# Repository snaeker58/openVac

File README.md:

# OpenVac - a custom motherboard

The goal of this project is to develop a fully functional motherboard to create an open-source autonomous vacuum robot.

 While the current goal is to get a functioning board for the Eufy RoboVac 11, the final goal should be something that can be used/adapted to work in all robot vacuums.

## Roadmap
*Nobody: This probably should go in a seperate file.*
### v0: Concept Phase
- **Goals**:
  - Define project objectives.
  - Determine core functionalities.
- **Basic Structure**:
  - Establish an initial project framework.
- **Key Components**:
  - **Motor Drive Circuit**: Design a DIY motor driver/H-bridge.
  - **Brush Control**: Develop circuits for controlling all cleaning brushes.
  - **Vacuum**: Identify and understand the pinout.
  - **Basic Sensing**: 
    - Understand various sensors.
    - Reverse-engineer the main sensor array.
    - Prototype edge sensors to achieve functionality.
- **Status**: **Finished**

### v0.1: Basic Movement
- **Movement Capabilities**:
  - Implement steering and acceleration.
- **PCB Development**:
  - **DIY Motor Drive Circuit**
  - **Side Brush Control Circuit**
  - **Main Brush Control Circuit**
  - **PWM Vacuum Control**
- **Status**: **Finished**

### v0.2: Minimum Viable Product (MVP)
- **Power & Batteries**:
  - Implement a Battery Management System (BMS).

  - Integrate lithium-ion batteries.

- **Control**:
  - Enable USB serial control for motors, brushes, and vacuum.
- **Miniaturization**:
  - Utilize off-the-shelf components for motor drive, BMS, and more.
- **Status**: **In progress (order placed)**

### v0.3: Basic Sensing
- **Sensor Development**:
  - Finalize cliff sensors (completed in v0).
  - Collect raw data from the main sensor array.
  - Implement a working bumper bar.
- **Sensing PCB**:
  - Develop basic signal processing to output usable data.

### Future Phases
- **Microprocessor Selection**:
  - Evaluate GPIO, analog input requirements, and performance needs.
- **Integration**:
  - **Hardware Integration**: Combine support circuits required by the microprocessor.
  - **Final PCB**: Connect all previous systems into a comprehensive PCB design.

### Far Future Goals
- **Navigational Software**: Create software for autonomous cleaning capabilities.
- **User Interface**: Develop an intuitive interface for easier and more precise control.

### Estimated Timeline
**3 years to infinity.**

## Contributing

If you're  mad enough to want to contribute then just tell me when I'm doing something wrong. I'm completely balling everything if you haven't noticed already. But hey I'm having fun.

"Start big or don't start!"

## Acknowledgements

 - I hereby acknowledge ChatGPT for having formatted my text and without me wanting it reworded my contents to sound more corporate.
 - I hereby acknowledge [Readme.so](https://readme.so) to have helped me make my readme look less ugly.

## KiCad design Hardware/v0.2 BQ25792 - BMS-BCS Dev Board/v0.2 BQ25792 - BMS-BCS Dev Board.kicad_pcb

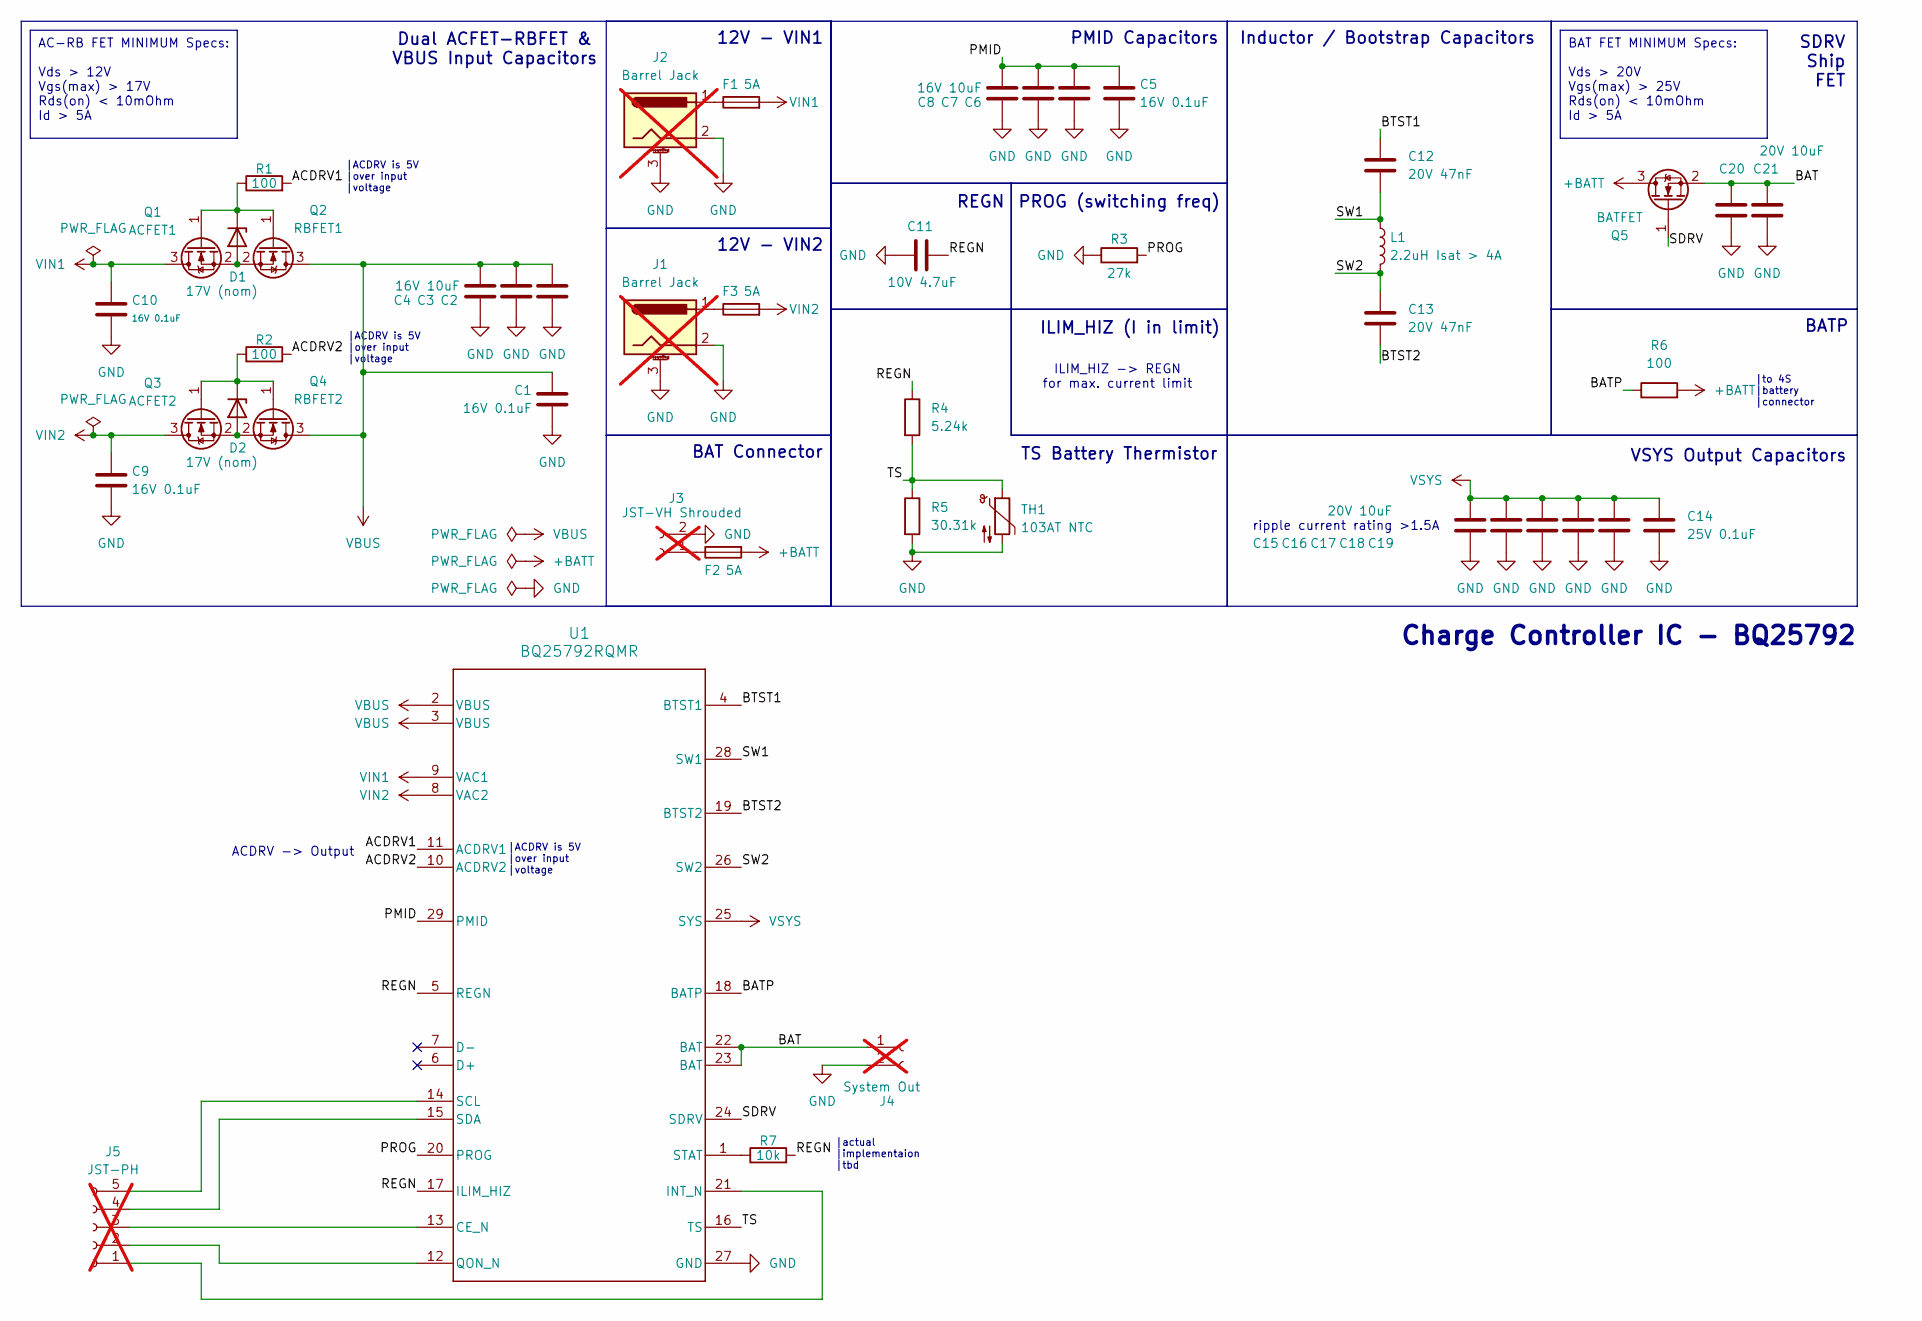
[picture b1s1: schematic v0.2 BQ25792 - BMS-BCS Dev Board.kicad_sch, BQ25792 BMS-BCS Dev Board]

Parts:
C1, C5, C9, C10: 16V 0.1uF; C_0402_1005Metric; LCSC Part Number C22435940
C2, C3, C4, C6, C7, C8: 16V 10uF; C_0603_1608Metric; LCSC Part Number C7472961
C11: 10V 4.7uF; C_0402_1005Metric; LCSC Part Number C466621
C12, C13: 20V 47nF; C_0402_1005Metric; LCSC Part Number C5142571
C14: 25V 0.1uF; C_0402_1005Metric; LCSC Part Number C22435940
C15, C16, C17, C18, C19, C20, C21: 20V 10uF; C_0603_1608Metric; LCSC Part Number C7472961
D1, D2: 17V (nom); D_SOD-123; LCSC Part Number C308704
F1, F2, F3: 5A; Fuse_0603_1608Metric; LCSC Part Number C206961
J1, J2: Barrel Jack; BarrelJack_GCT_DCJ200-10-A_Horizontal; not fitted
J3: JST-VH Shrouded; JST_VH_B2P-VH-FB-B_1x02_P3.96mm_Vertical; not fitted
J4: System Out; JST_VH_B2P-VH-FB-B_1x02_P3.96mm_Vertical; not fitted
J5: JST-PH; JST_PH_B5B-PH-K_1x05_P2.00mm_Vertical; not fitted
L1: 2.2uH Isat > 4A; L_4.5x4.1_H2; LCSC Part Number C22463806
Q1: ACFET1; SOT-23; LCSC Part Number C915719
Q2: RBFET1; SOT-23; LCSC Part Number C915719
Q3: ACFET2; SOT-23; LCSC Part Number C915719
Q4: RBFET2; SOT-23; LCSC Part Number C915719
Q5: BATFET; SOT-23-3L; LCSC Part Number C3033398
R1, R2, R6: 100; R_0402_1005Metric; LCSC Part Number C2906884
R3: 27k; R_0402_1005Metric; LCSC Part Number C2929913
R4: 5.24k; R_0402_1005Metric; LCSC Part Number C11631
R5: 30.31k; R_0402_1005Metric; LCSC Part Number C4156287
R7: 10k; R_0402_1005Metric; LCSC Part Number C2906885
TH1: 103AT NTC; JST_PH_B2B-PH-K_1x02_P2.00mm_Vertical; LCSC Part Number C497233
U1: BQ25792RQMR; RQM0029A-MFG; LCSC Part Number C2862876

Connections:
+BATT: F2.2, Q5.3 (D), R6.2
/ACDRV1: R1.2, U1.11 (ACDRV1)
/ACDRV2: R2.2, U1.10 (ACDRV2)
/BAT: C20.2, C21.2, J4.1, Q5.2 (S), U1.22 (BAT), U1.23 (BAT)
/BATP: R6.1, U1.18 (BATP)
/BTST1: C12.2, U1.4 (BTST1)
/BTST2: C13.1, U1.19 (BTST2)
/PMID: C5.1, C6.2, C7.2, C8.2, U1.29 (PMID)
/PROG: R3.2, U1.20 (PROG)
/REGN: C11.1, R4.1, R7.2, U1.5 (REGN), U1.17 (ILIM_HIZ)
/SDRV: Q5.1 (G), U1.24 (SDRV)
/SW1: C12.1, L1.1, U1.28 (SW1)
/SW2: C13.2, L1.2, U1.26 (SW2)
/TS: R4.2, R5.1, TH1.1, U1.16 (TS)
GND: C1.2, C2.1, C3.1, C4.1, C5.2, C6.1, C7.1, C8.1, C9.2, C10.2, C11.2, C14.2, C15.1, C16.1, C17.1, C18.1, C19.1, C20.1, C21.1, J1.2, J1.3 (MountPin), J2.2, J2.3 (MountPin), J3.2, J4.2, R3.1, R5.2, TH1.2, U1.27 (GND)
unnamed: D1.2 (A), Q1.2 (S), Q2.2 (S)
unnamed: D1.1 (K), Q1.1 (G), Q2.1 (G), R1.1
unnamed: D2.2 (A), Q3.2 (S), Q4.2 (S)
unnamed: D2.1 (K), Q3.1 (G), Q4.1 (G), R2.1
unnamed: F1.1, J2.1
unnamed: F3.1, J1.1
unnamed: F2.1, J3.1
unnamed: J5.1, U1.21 (INT_N)
unnamed: J5.2, U1.12 (QON_N)
unnamed: J5.3, U1.13 (CE_N)
unnamed: J5.4, U1.15 (SDA)
unnamed: J5.5, U1.14 (SCL)
unnamed: R7.1, U1.1 (STAT)
VBUS: C1.1, C2.2, C3.2, C4.2, Q2.3 (D), Q4.3 (D), U1.2 (VBUS), U1.3 (VBUS)
VIN1: C10.1, F1.2, Q1.3 (D), U1.9 (VAC1)
VIN2: C9.1, F3.2, Q3.3 (D), U1.8 (VAC2)
VSYS: C14.1, C15.2, C16.2, C17.2, C18.2, C19.2, U1.25 (SYS)

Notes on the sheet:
BAT FET MINIMUM Specs: Vds > 20V Vgs(max) > 25V Rds(on) < 10mOhm Id > 5A
AC-RB FET MINIMUM Specs: Vds > 12V Vgs(max) > 17V Rds(on) < 10mOhm Id > 5A
TS Battery Thermistor
Inductor / Bootstrap Capacitors
ripple current rating >1.5A
BAT Connector
SDRV Ship FET
|actual |implementaion |tbd
VSYS Output Capacitors
Dual ACFET-RBFET & VBUS Input Capacitors
PROG (switching freq)
|ACDRV is 5V |over input |voltage
ACDRV -> Output
ILIM_HIZ (I in limit)
Charge Controller IC - BQ25792
REGN
12V - VIN1
|to 4S |battery |connector
ILIM_HIZ -> REGN for max. current limit
PMID Capacitors
BATP
12V - VIN2

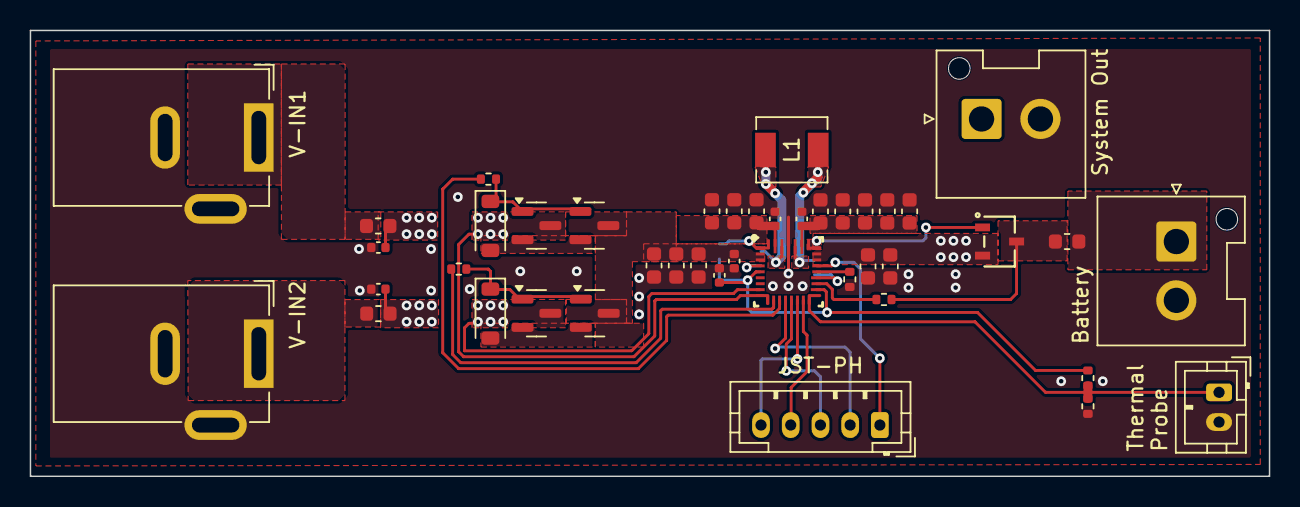
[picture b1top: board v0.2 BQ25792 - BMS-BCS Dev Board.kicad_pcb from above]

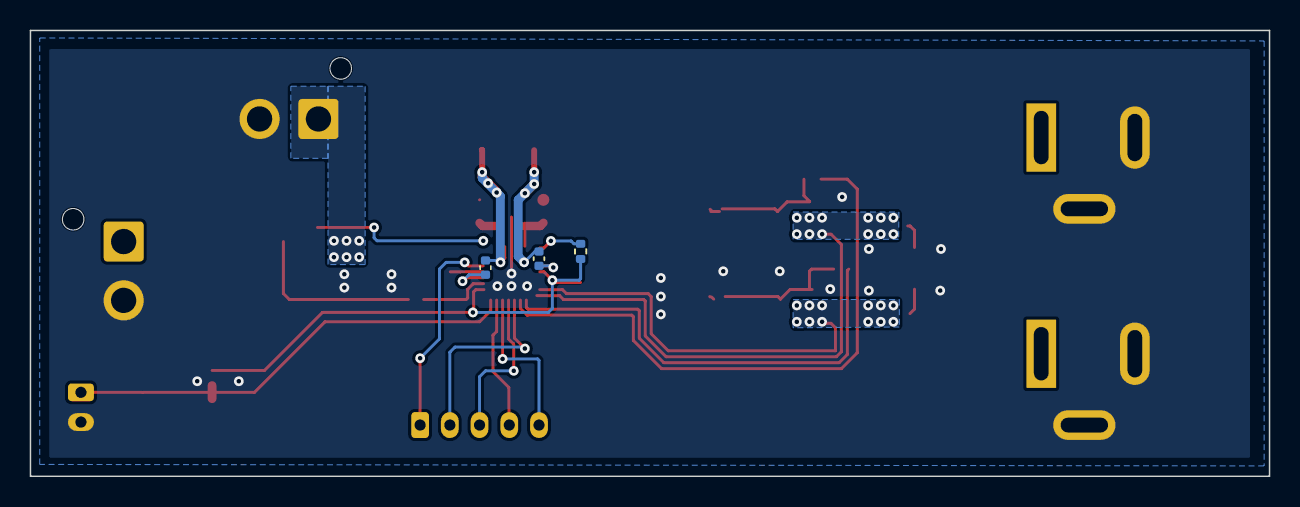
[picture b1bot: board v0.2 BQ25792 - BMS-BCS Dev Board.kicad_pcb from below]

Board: 2 copper layers, 83.4 x 30.0 mm, 46 parts (3 on the bottom side), 32 nets.

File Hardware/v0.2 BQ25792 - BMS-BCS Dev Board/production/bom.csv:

Designator,Footprint,Quantity,Value,LCSC Part #
"C1, C10, C5, C9",0402,4,16V 0.1uF,C22435940
C11,0402,1,10V 4.7uF,C466621
"C12, C13",0402,2,20V 47nF,C5142571
C14,0402,1,25V 0.1uF,C22435940
"C15, C16, C17, C18, C19, C20, C21",0603,7,20V 10uF,C7472961
"C2, C3, C4, C6, C7, C8",0603,6,16V 10uF,C7472961
"D1, D2",D_SOD-123,2,17V (nom),C308704
"F1, F2, F3",0603,3,5A,C206961
L1,L_4.5x4.1_H2,1,2.2uH Isat > 4A,C22463806
Q1,SOT-23,1,ACFET1,C915719
Q2,SOT-23,1,RBFET1,C915719
Q3,SOT-23,1,ACFET2,C915719
Q4,SOT-23,1,RBFET2,C915719
Q5,SOT-23-3L,1,BATFET,C3033398
"R1, R2, R6",0402,3,100,C2906884
R3,0402,1,27k,C2929913
R4,0402,1,5.24k,C11631
R5,0402,1,30.31k,C2998131
R7,0402,1,10k,C2906885
U1,RQM0029A-MFG,1,BQ25792RQMR,C2862876

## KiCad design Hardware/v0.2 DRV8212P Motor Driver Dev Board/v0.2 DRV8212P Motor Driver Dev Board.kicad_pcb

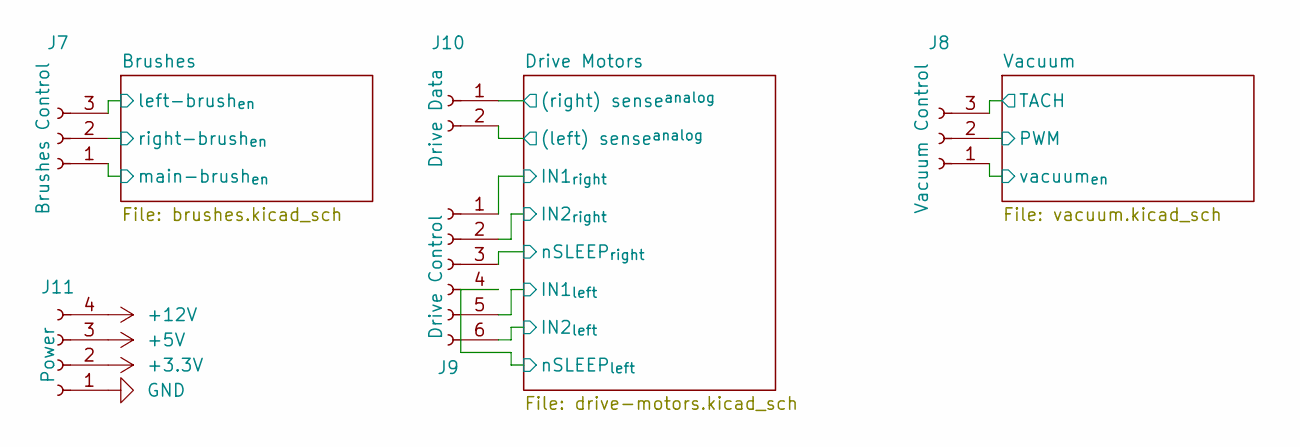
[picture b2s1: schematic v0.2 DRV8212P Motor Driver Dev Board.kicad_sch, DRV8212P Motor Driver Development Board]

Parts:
J7: Brushes Control; JST_PH_B3B-PH-K_1x03_P2.00mm_Vertical
J8: Vacuum Control; JST_PH_B3B-PH-K_1x03_P2.00mm_Vertical
J9: Drive Control; JST_PH_B6B-PH-K_1x06_P2.00mm_Vertical
J10: Drive Data; JST_PH_B2B-PH-K_1x02_P2.00mm_Vertical
J11: Power; JST_PH_B4B-PH-K_1x04_P2.00mm_Vertical

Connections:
+3.3V: J11.2; also elsewhere on the board
+5V: J11.3; also elsewhere on the board
+12V: J11.4; also elsewhere on the board
/Brushes/left-brush_{en}: J7.3; also elsewhere on the board
/Brushes/main-brush_{en}: J7.1; also elsewhere on the board
/Brushes/right-brush_{en}: J7.2; also elsewhere on the board
/Drive Motors/(left) sense^{analog}: J10.2; also elsewhere on the board
/Drive Motors/(right) sense^{analog}: J10.1; also elsewhere on the board
/Drive Motors/IN1_{left}: J9.5; also elsewhere on the board
/Drive Motors/IN1_{right}: J9.1; also elsewhere on the board
/Drive Motors/IN2_{left}: J9.6; also elsewhere on the board
/Drive Motors/IN2_{right}: J9.2; also elsewhere on the board
/Drive Motors/nSLEEP_{left}: J9.4; also elsewhere on the board
/Drive Motors/nSLEEP_{right}: J9.3; also elsewhere on the board
/Vacuum/PWM: J8.2; also elsewhere on the board
/Vacuum/TACH: J8.3; also elsewhere on the board
/Vacuum/vacuum_{en}: J8.1; also elsewhere on the board
GND: J11.1; also elsewhere on the board

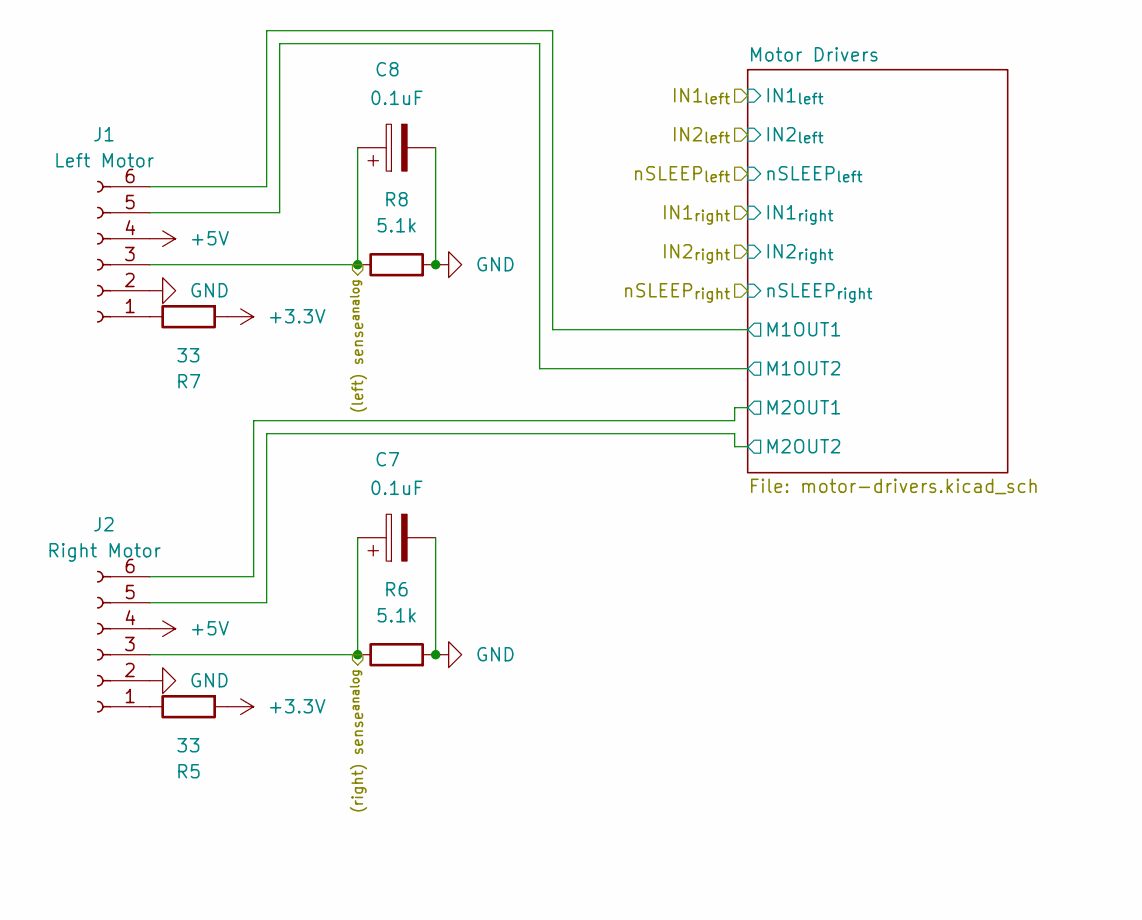
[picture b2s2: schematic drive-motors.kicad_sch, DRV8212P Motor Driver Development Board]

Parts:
C7, C8: 0.1uF; C_0603_1608Metric_Pad1.08x0.95mm_HandSolder
J1: Left Motor; JST_PH_B6B-PH-K_1x06_P2.00mm_Vertical
J2: Right Motor; JST_PH_B6B-PH-K_1x06_P2.00mm_Vertical
R5, R7: 33; R_0603_1608Metric_Pad0.98x0.95mm_HandSolder
R6, R8: 5.1k; R_0603_1608Metric_Pad0.98x0.95mm_HandSolder

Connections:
+3.3V: R5.2, R7.2; also elsewhere on the board
+5V: J1.4, J2.4; also elsewhere on the board
/Drive Motors/(left) sense^{analog}: C8.1, J1.3, R8.1; also elsewhere on the board
/Drive Motors/(right) sense^{analog}: C7.1, J2.3, R6.1; also elsewhere on the board
/Drive Motors/Motor Drivers/M1OUT1: J1.6; also elsewhere on the board
/Drive Motors/Motor Drivers/M1OUT2: J1.5; also elsewhere on the board
/Drive Motors/Motor Drivers/M2OUT1: J2.6; also elsewhere on the board
/Drive Motors/Motor Drivers/M2OUT2: J2.5; also elsewhere on the board
GND: C7.2, C8.2, J1.2, J2.2, R6.2, R8.2; also elsewhere on the board
unnamed: J1.1, R7.1
unnamed: J2.1, R5.1

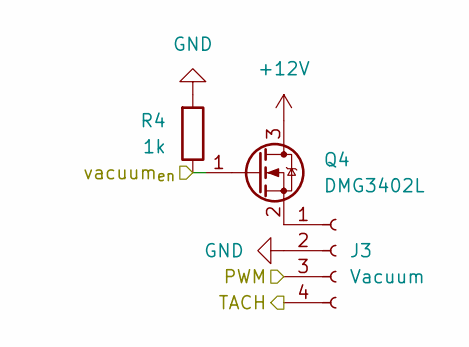
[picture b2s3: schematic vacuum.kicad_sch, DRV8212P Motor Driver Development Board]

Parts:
J3: Vacuum; JST_PH_B4B-PH-K_1x04_P2.00mm_Vertical
Q4: DMG3402L; SOT-23
R4: 1k; R_0603_1608Metric_Pad0.98x0.95mm_HandSolder

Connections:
+12V: Q4.3 (D); also elsewhere on the board
/Vacuum/PWM: J3.3; also elsewhere on the board
/Vacuum/TACH: J3.4; also elsewhere on the board
/Vacuum/vacuum_{en}: Q4.1 (G), R4.1; also elsewhere on the board
GND: J3.2, R4.2; also elsewhere on the board
unnamed: J3.1, Q4.2 (S)

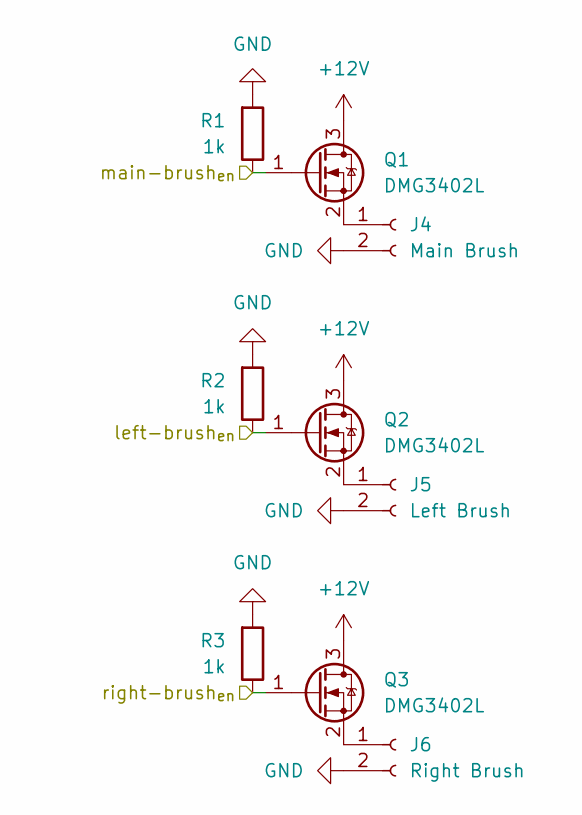
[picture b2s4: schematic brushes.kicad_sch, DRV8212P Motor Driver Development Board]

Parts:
J4: Main Brush; JST_PH_B2B-PH-K_1x02_P2.00mm_Vertical
J5: Left Brush; JST_PH_B2B-PH-K_1x02_P2.00mm_Vertical
J6: Right Brush; JST_PH_B2B-PH-K_1x02_P2.00mm_Vertical
Q1, Q2, Q3: DMG3402L; SOT-23
R1, R2, R3: 1k; R_0603_1608Metric_Pad0.98x0.95mm_HandSolder

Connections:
+12V: Q1.3 (D), Q2.3 (D), Q3.3 (D); also elsewhere on the board
/Brushes/left-brush_{en}: Q2.1 (G), R2.1; also elsewhere on the board
/Brushes/main-brush_{en}: Q1.1 (G), R1.1; also elsewhere on the board
/Brushes/right-brush_{en}: Q3.1 (G), R3.1; also elsewhere on the board
GND: J4.2, J5.2, J6.2, R1.2, R2.2, R3.2; also elsewhere on the board
unnamed: J4.1, Q1.2 (S)
unnamed: J5.1, Q2.2 (S)
unnamed: J6.1, Q3.2 (S)

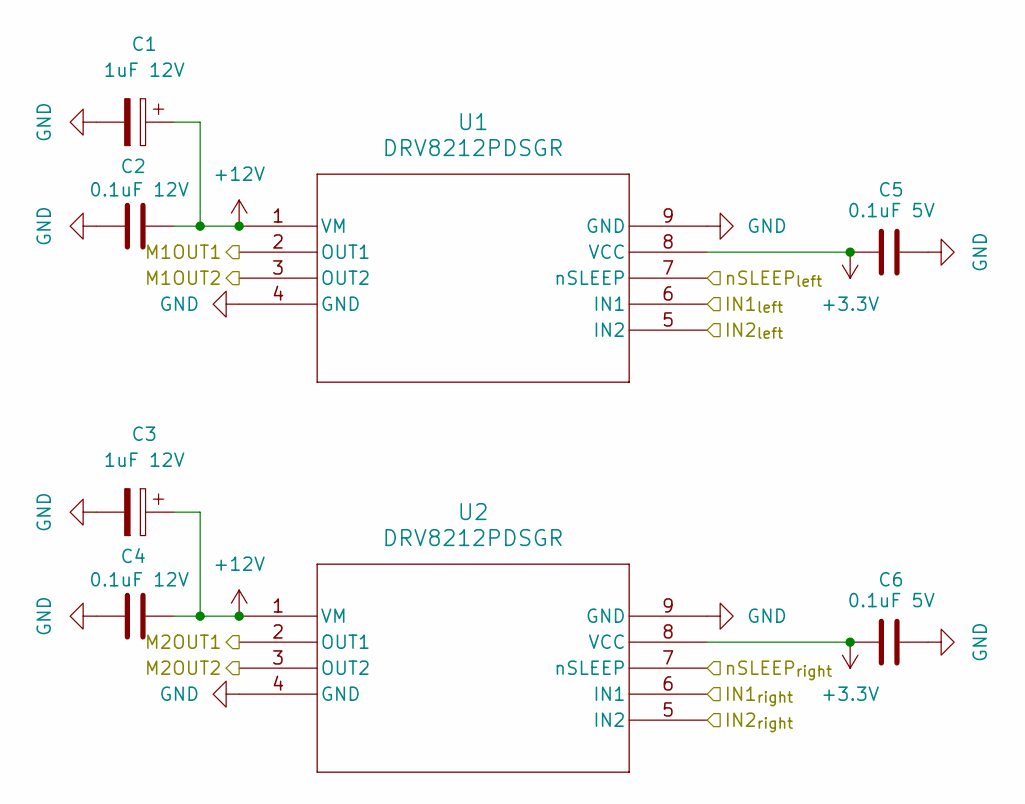
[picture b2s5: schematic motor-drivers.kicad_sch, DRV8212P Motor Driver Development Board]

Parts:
C1, C3: 1uF 12V; C_0603_1608Metric_Pad1.08x0.95mm_HandSolder
C2, C4: 0.1uF 12V; C_0603_1608Metric_Pad1.08x0.95mm_HandSolder
C5, C6: 0.1uF 5V; C_0603_1608Metric_Pad1.08x0.95mm_HandSolder
U1, U2: DRV8212PDSGR; WSON8_DSG_TEX

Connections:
+3.3V: C5.1, C6.1, U1.8 (VCC), U2.8 (VCC); also elsewhere on the board
+12V: C1.1, C2.1, C3.1, C4.1, U1.1 (VM), U2.1 (VM); also elsewhere on the board
/Drive Motors/IN1_{left}: U1.6 (IN1); also elsewhere on the board
/Drive Motors/IN1_{right}: U2.6 (IN1); also elsewhere on the board
/Drive Motors/IN2_{left}: U1.5 (IN2); also elsewhere on the board
/Drive Motors/IN2_{right}: U2.5 (IN2); also elsewhere on the board
/Drive Motors/Motor Drivers/M1OUT1: U1.2 (OUT1); also elsewhere on the board
/Drive Motors/Motor Drivers/M1OUT2: U1.3 (OUT2); also elsewhere on the board
/Drive Motors/Motor Drivers/M2OUT1: U2.2 (OUT1); also elsewhere on the board
/Drive Motors/Motor Drivers/M2OUT2: U2.3 (OUT2); also elsewhere on the board
/Drive Motors/nSLEEP_{left}: U1.7 (nSLEEP); also elsewhere on the board
/Drive Motors/nSLEEP_{right}: U2.7 (nSLEEP); also elsewhere on the board
GND: C1.2, C2.2, C3.2, C4.2, C5.2, C6.2, U1.4 (GND), U1.9 (GND), U2.4 (GND), U2.9 (GND); also elsewhere on the board

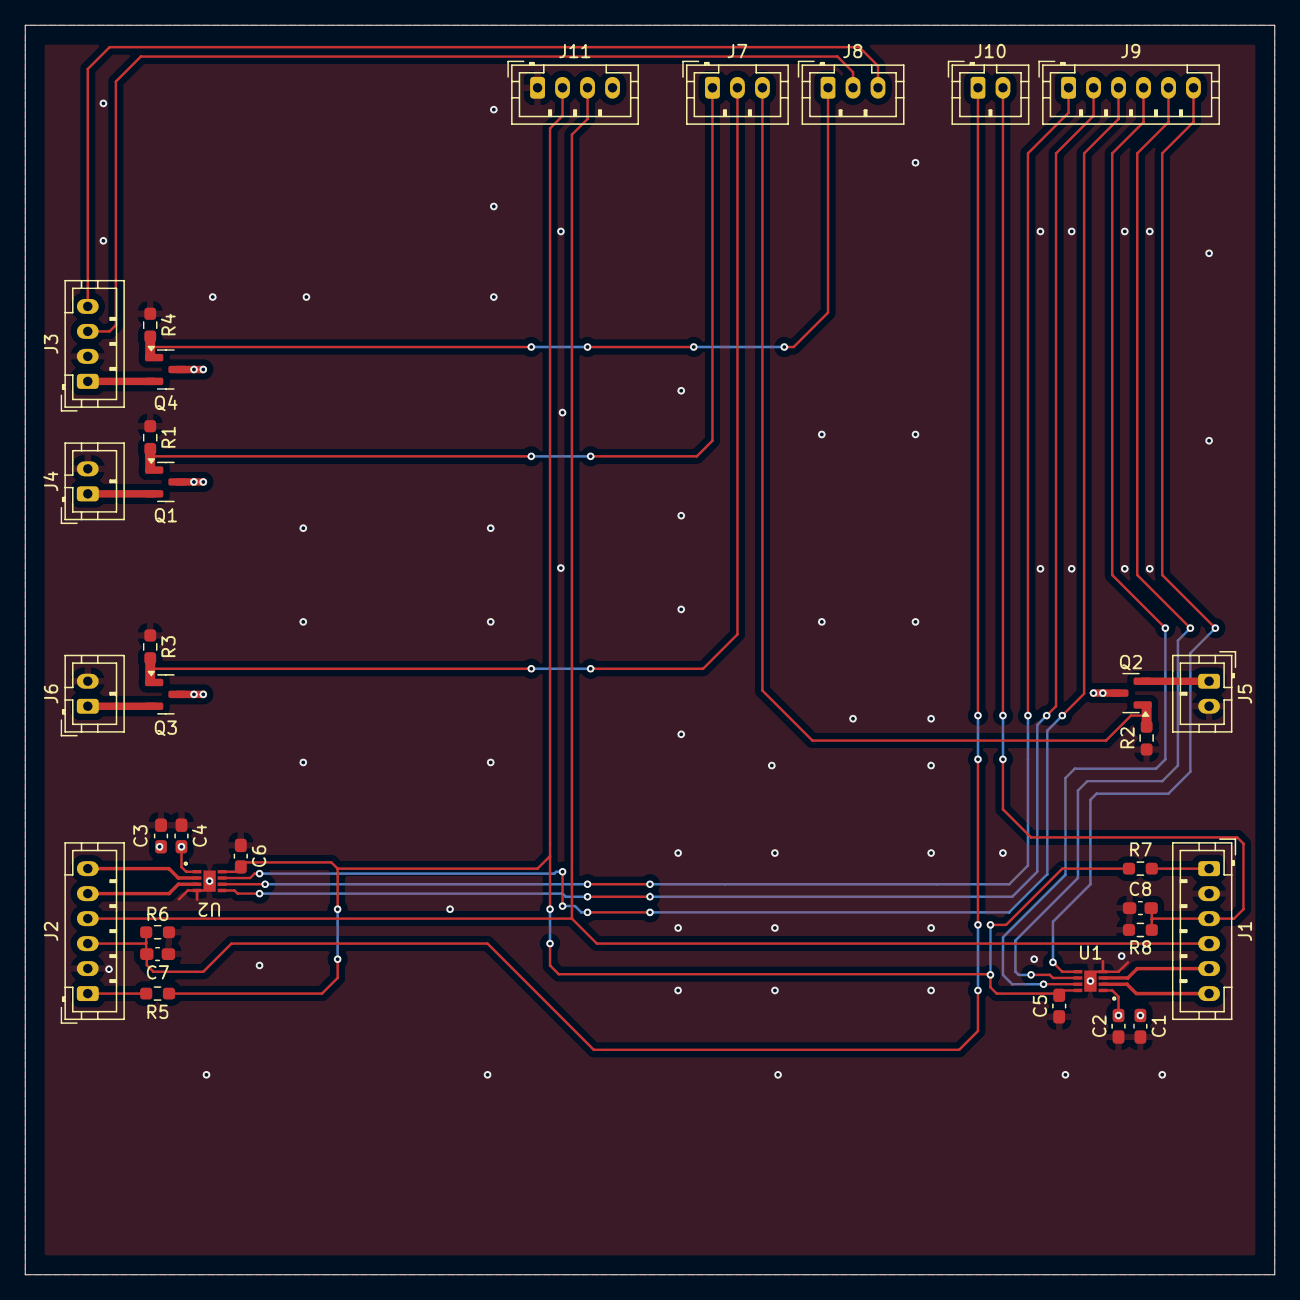
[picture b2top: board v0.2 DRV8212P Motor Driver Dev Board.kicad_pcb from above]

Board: 2 copper layers, 100.0 x 100.0 mm, 33 parts (0 on the bottom side), 28 nets.

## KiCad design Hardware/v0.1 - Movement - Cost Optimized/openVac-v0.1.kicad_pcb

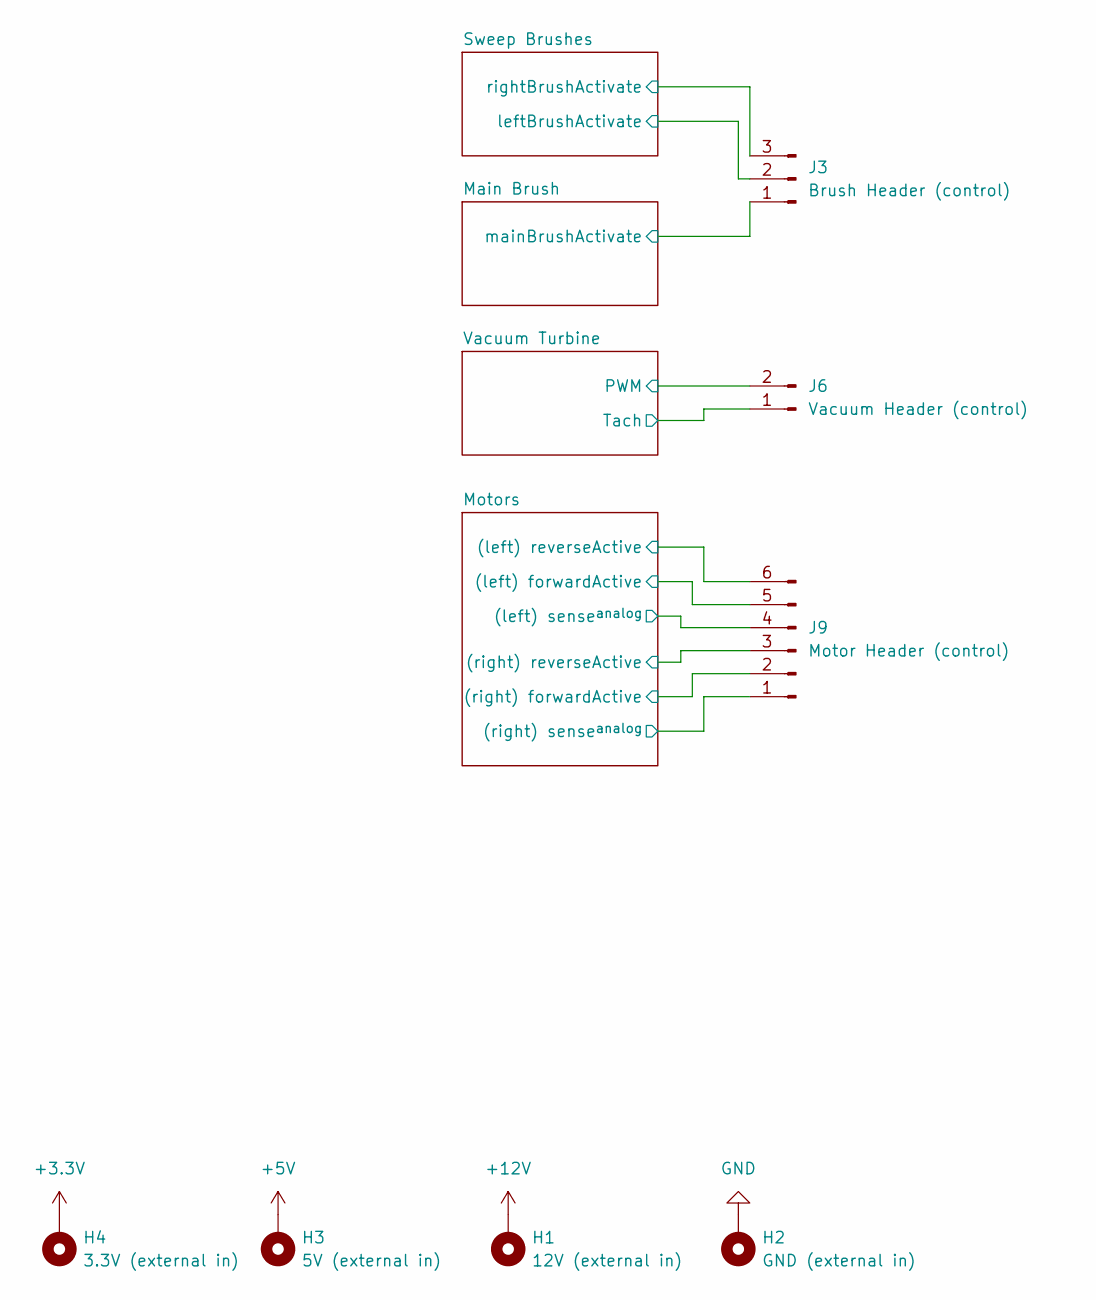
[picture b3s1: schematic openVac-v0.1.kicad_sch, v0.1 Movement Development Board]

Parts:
H1: 12V (external in); MountingHole_2.2mm_M2_DIN965_Pad
H2: GND (external in); MountingHole_2.2mm_M2_DIN965_Pad
H3: 5V (external in); MountingHole_2.2mm_M2_DIN965_Pad
H4: 3.3V (external in); MountingHole_2.2mm_M2_DIN965_Pad
J3: Brush Header (control); JST_PH_B3B-PH-K_1x03_P2.00mm_Vertical
J6: Vacuum Header (control); JST_PH_B2B-PH-K_1x02_P2.00mm_Vertical
J9: Motor Header (control); JST_PH_B6B-PH-K_1x06_P2.00mm_Vertical

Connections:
+3.3V: H4.1; also elsewhere on the board
+5V: H3.1; also elsewhere on the board
+12V: H1.1; also elsewhere on the board
/Main Brush/mainBrushActivate: J3.1; also elsewhere on the board
/Motors/(left) forwardActive: J9.5; also elsewhere on the board
/Motors/(left) reverseActive: J9.6; also elsewhere on the board
/Motors/(left) sense^{analog}: J9.4; also elsewhere on the board
/Motors/(right) forwardActive: J9.2; also elsewhere on the board
/Motors/(right) reverseActive: J9.3; also elsewhere on the board
/Motors/(right) sense^{analog}: J9.1; also elsewhere on the board
/Sweep Brushes/leftBrushActivate: J3.2; also elsewhere on the board
/Sweep Brushes/rightBrushActivate: J3.3; also elsewhere on the board
/Vacuum Turbine/PWM: J6.2; also elsewhere on the board
/Vacuum Turbine/Tach: J6.1; also elsewhere on the board
GND: H2.1; also elsewhere on the board

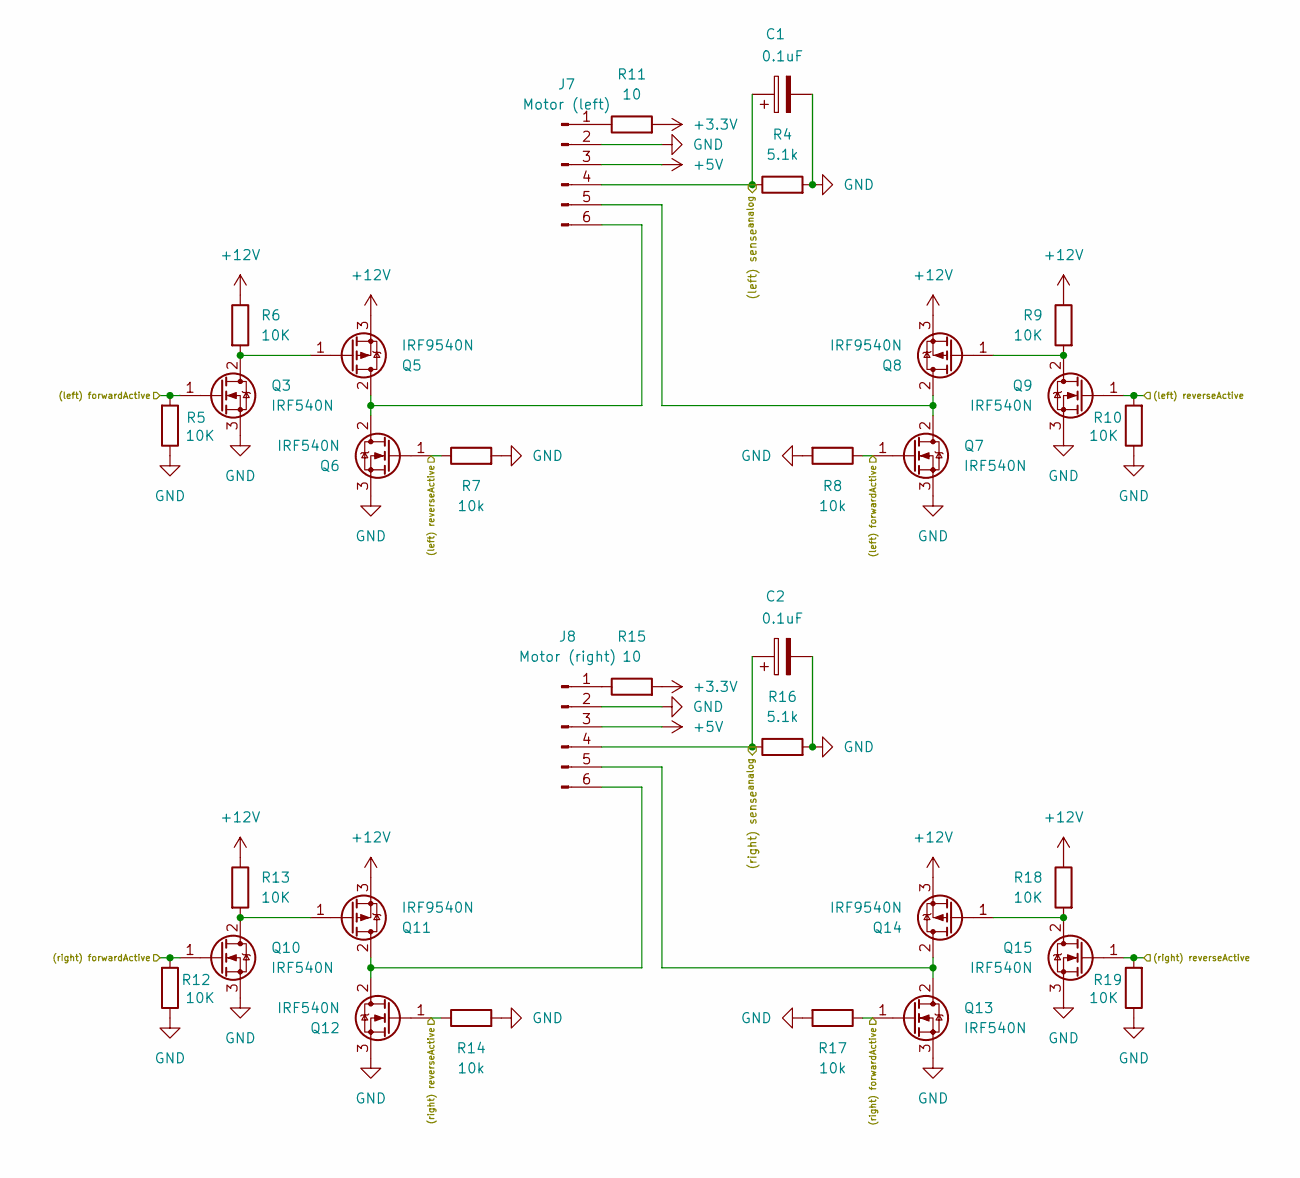
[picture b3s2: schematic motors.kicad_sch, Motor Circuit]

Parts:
C1, C2: 0.1uF; CP_Radial_D4.0mm_P1.50mm
J7: Motor (left); JST_PH_B6B-PH-K_1x06_P2.00mm_Vertical
J8: Motor (right); JST_PH_B6B-PH-K_1x06_P2.00mm_Vertical
Q3, Q6, Q7, Q9, Q10, Q12, Q13, Q15: IRF540N; TO-220-3_Vertical
Q5, Q8, Q11, Q14: IRF9540N; TO-220-3_Vertical
R4, R16: 5.1k; R_Axial_DIN0207_L6.3mm_D2.5mm_P10.16mm_Horizontal
R5, R6, R9, R10, R12, R13, R18, R19: 10K; R_Axial_DIN0207_L6.3mm_D2.5mm_P10.16mm_Horizontal
R7, R8, R14, R17: 10k; R_Axial_DIN0207_L6.3mm_D2.5mm_P10.16mm_Horizontal
R11, R15: 10; R_Axial_DIN0207_L6.3mm_D2.5mm_P10.16mm_Horizontal

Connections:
+3.3V: R11.2, R15.2; also elsewhere on the board
+5V: J7.3, J8.3; also elsewhere on the board
+12V: Q5.3 (S), Q8.3 (S), Q11.3 (S), Q14.3 (S), R6.1, R9.1, R13.1, R18.1; also elsewhere on the board
/Motors/(left) forwardActive: Q3.1 (G), Q7.1 (G), R5.2, R8.1; also elsewhere on the board
/Motors/(left) reverseActive: Q6.1 (G), Q9.1 (G), R7.1, R10.2; also elsewhere on the board
/Motors/(left) sense^{analog}: C1.1, J7.4, R4.1; also elsewhere on the board
/Motors/(right) forwardActive: Q10.1 (G), Q13.1 (G), R12.2, R17.1; also elsewhere on the board
/Motors/(right) reverseActive: Q12.1 (G), Q15.1 (G), R14.1, R19.2; also elsewhere on the board
/Motors/(right) sense^{analog}: C2.1, J8.4, R16.1; also elsewhere on the board
GND: C1.2, C2.2, J7.2, J8.2, Q3.3 (S), Q6.3 (S), Q7.3 (S), Q9.3 (S), Q10.3 (S), Q12.3 (S), Q13.3 (S), Q15.3 (S), R4.2, R5.1, R7.2, R8.2, R10.1, R12.1, R14.2, R16.2, R17.2, R19.1; also elsewhere on the board
unnamed: J7.1, R11.1
unnamed: J7.5, Q7.2 (D), Q8.2 (D)
unnamed: J7.6, Q5.2 (D), Q6.2 (D)
unnamed: J8.1, R15.1
unnamed: J8.5, Q13.2 (D), Q14.2 (D)
unnamed: J8.6, Q11.2 (D), Q12.2 (D)
unnamed: Q3.2 (D), Q5.1 (G), R6.2
unnamed: Q8.1 (G), Q9.2 (D), R9.2
unnamed: Q10.2 (D), Q11.1 (G), R13.2
unnamed: Q14.1 (G), Q15.2 (D), R18.2

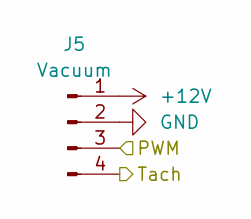
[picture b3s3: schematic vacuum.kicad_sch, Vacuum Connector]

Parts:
J5: Vacuum; JST_PH_B4B-PH-K_1x04_P2.00mm_Vertical

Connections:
+12V: J5.1; also elsewhere on the board
/Vacuum Turbine/PWM: J5.3; also elsewhere on the board
/Vacuum Turbine/Tach: J5.4; also elsewhere on the board
GND: J5.2; also elsewhere on the board

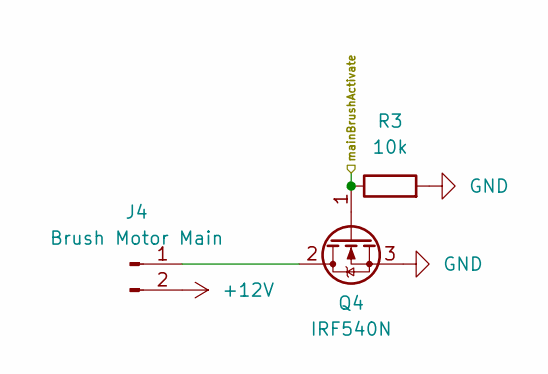
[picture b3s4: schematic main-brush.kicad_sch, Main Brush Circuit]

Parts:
J4: Brush Motor Main; JST_PH_B2B-PH-K_1x02_P2.00mm_Vertical
Q4: IRF540N; TO-220-3_Vertical
R3: 10k; R_Axial_DIN0207_L6.3mm_D2.5mm_P10.16mm_Horizontal

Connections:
+12V: J4.2; also elsewhere on the board
/Main Brush/mainBrushActivate: Q4.1 (G), R3.1; also elsewhere on the board
GND: Q4.3 (S), R3.2; also elsewhere on the board
unnamed: J4.1, Q4.2 (D)

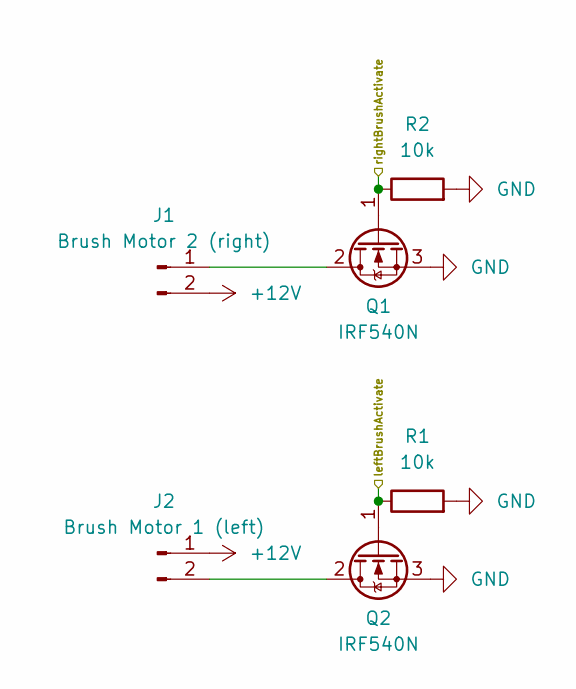
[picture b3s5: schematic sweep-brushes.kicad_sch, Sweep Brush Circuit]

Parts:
J1: Brush Motor 2 (right); JST_PH_B2B-PH-K_1x02_P2.00mm_Vertical
J2: Brush Motor 1 (left); JST_PH_B2B-PH-K_1x02_P2.00mm_Vertical
Q1, Q2: IRF540N; TO-220-3_Vertical
R1, R2: 10k; R_Axial_DIN0207_L6.3mm_D2.5mm_P10.16mm_Horizontal

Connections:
+12V: J1.2, J2.1; also elsewhere on the board
/Sweep Brushes/leftBrushActivate: Q2.1 (G), R1.1; also elsewhere on the board
/Sweep Brushes/rightBrushActivate: Q1.1 (G), R2.1; also elsewhere on the board
GND: Q1.3 (S), Q2.3 (S), R1.2, R2.2; also elsewhere on the board
unnamed: J1.1, Q1.2 (D)
unnamed: J2.2, Q2.2 (D)
